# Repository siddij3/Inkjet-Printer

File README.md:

# Inkjet-Printer

DIY Inkjet Printer using Rep-Rap 3D Printing inspired parts and components

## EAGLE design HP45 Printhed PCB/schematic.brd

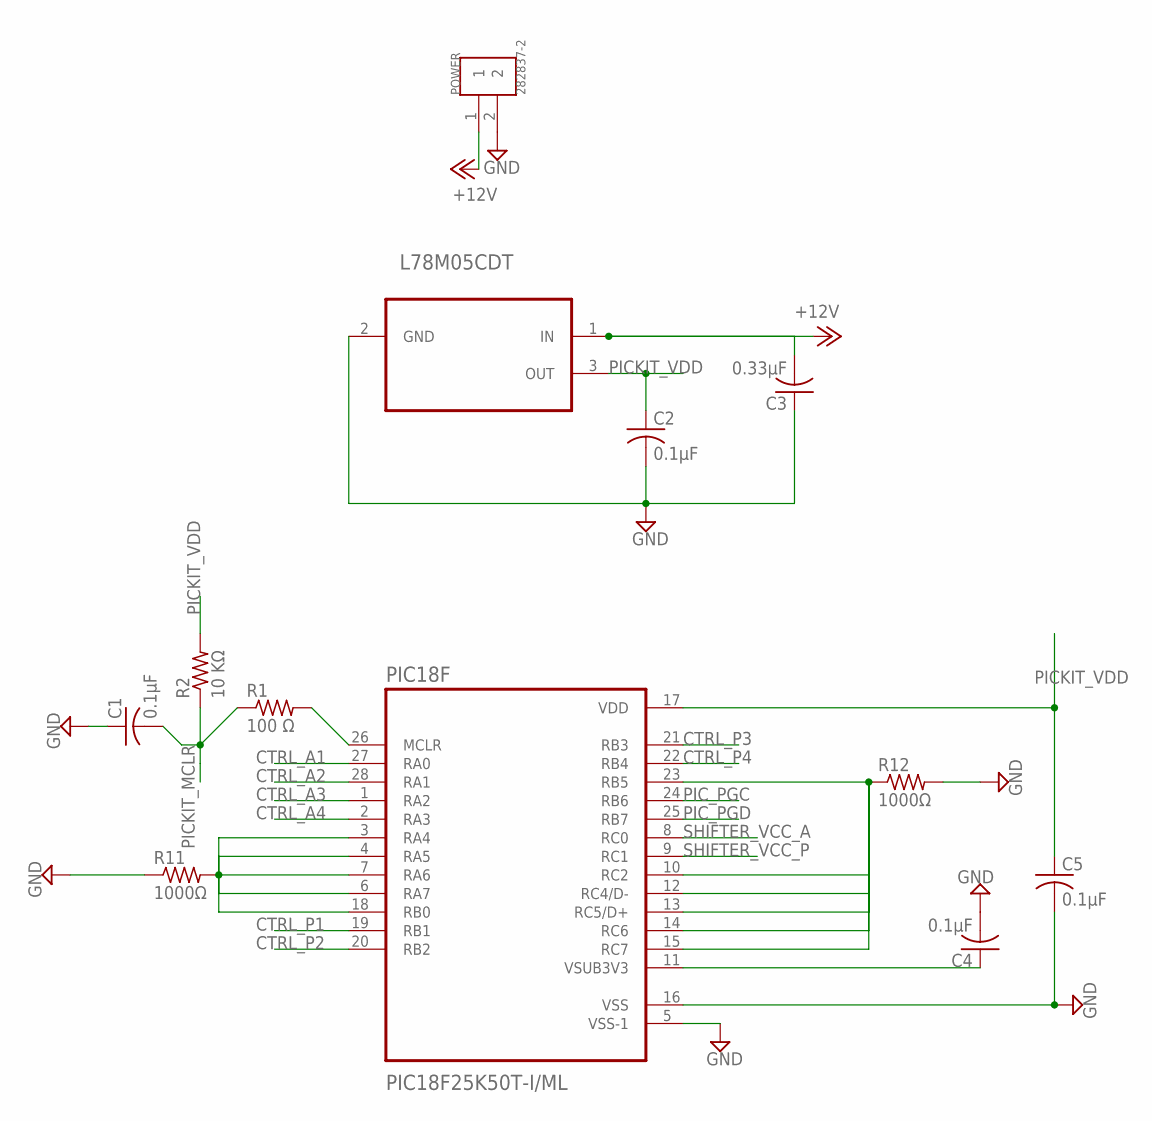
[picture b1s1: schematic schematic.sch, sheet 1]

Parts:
C1, C2, C4, C5: 0.1µF; C0603; MPN B32529C0104J000
C3: 0.33µF; C0603
L78M05CDT: L78M05CDT; TO225P972X240-3N
PIC18F: PIC18F25K50T-I/ML; QFN65P600X600X100-29N
POWER: 282837-2; TE_282837-2
R1: 100 Ω; R0805
R2: 10 KΩ; R0805
R11, R12: 1000Ω; R0603

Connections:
+12V: C3.2, L78M05CDT.1 (IN), POWER.1; also elsewhere on the board
CTRL_A1: PIC18F.27 (RA0); also elsewhere on the board
CTRL_A2: PIC18F.28 (RA1); also elsewhere on the board
CTRL_A3: PIC18F.1 (RA2); also elsewhere on the board
CTRL_A4: PIC18F.2 (RA3); also elsewhere on the board
CTRL_P1: PIC18F.19 (RB1); also elsewhere on the board
CTRL_P2: PIC18F.20 (RB2); also elsewhere on the board
CTRL_P3: PIC18F.21 (RB3); also elsewhere on the board
CTRL_P4: PIC18F.22 (RB4); also elsewhere on the board
GND: C1.1, C2.2, C3.1, C4.2, C5.2, L78M05CDT.2 (GND), PIC18F.5 (VSS-1), PIC18F.16 (VSS), POWER.2, R11.1, R12.2; also elsewhere on the board
unnamed: C4.1, PIC18F.11 (VSUB3V3)
unnamed: PIC18F.3 (RA4), PIC18F.4 (RA5), PIC18F.6 (RA7), PIC18F.7 (RA6), PIC18F.18 (RB0), R11.2
unnamed: PIC18F.26 (MCLR), R1.2
unnamed: PIC18F.10 (RC2), PIC18F.12 (RC4/D-), PIC18F.13 (RC5/D+), PIC18F.14 (RC6), PIC18F.15 (RC7), PIC18F.23 (RB5), R12.1
PICKIT_MCLR: C1.2, R1.1, R2.1; also elsewhere on the board
PICKIT_VDD: C2.1, C5.1, L78M05CDT.3 (OUT), PIC18F.17 (VDD), R2.2; also elsewhere on the board
PIC_PGC: PIC18F.24 (RB6); also elsewhere on the board
PIC_PGD: PIC18F.25 (RB7); also elsewhere on the board
SHIFTER_VCC_A: PIC18F.8 (RC0); also elsewhere on the board
SHIFTER_VCC_P: PIC18F.9 (RC1); also elsewhere on the board

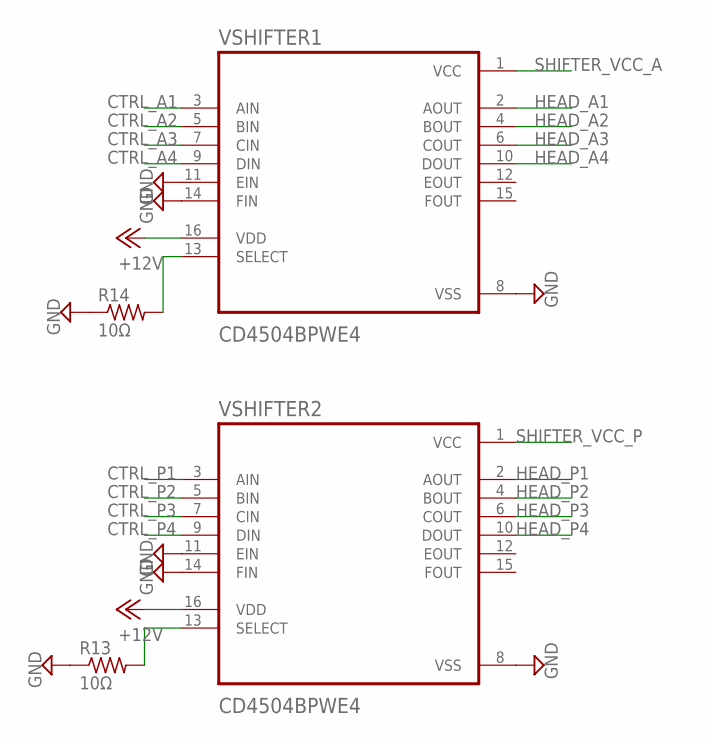
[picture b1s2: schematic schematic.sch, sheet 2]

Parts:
R13, R14: 10Ω; R0603
VSHIFTER1, VSHIFTER2: CD4504BPWE4; SOP65P640X120-16N

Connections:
+12V: VSHIFTER1.16 (VDD), VSHIFTER2.16 (VDD); also elsewhere on the board
CTRL_A1: VSHIFTER1.3 (AIN); also elsewhere on the board
CTRL_A2: VSHIFTER1.5 (BIN); also elsewhere on the board
CTRL_A3: VSHIFTER1.7 (CIN); also elsewhere on the board
CTRL_A4: VSHIFTER1.9 (DIN); also elsewhere on the board
CTRL_P1: VSHIFTER2.3 (AIN); also elsewhere on the board
CTRL_P2: VSHIFTER2.5 (BIN); also elsewhere on the board
CTRL_P3: VSHIFTER2.7 (CIN); also elsewhere on the board
CTRL_P4: VSHIFTER2.9 (DIN); also elsewhere on the board
GND: R13.1, R14.1, VSHIFTER1.8 (VSS), VSHIFTER1.11 (EIN), VSHIFTER1.14 (FIN), VSHIFTER2.8 (VSS), VSHIFTER2.11 (EIN), VSHIFTER2.14 (FIN); also elsewhere on the board
HEAD_A1: VSHIFTER1.2 (AOUT); also elsewhere on the board
HEAD_A2: VSHIFTER1.4 (BOUT); also elsewhere on the board
HEAD_A3: VSHIFTER1.6 (COUT); also elsewhere on the board
HEAD_A4: VSHIFTER1.10 (DOUT); also elsewhere on the board
HEAD_P1: VSHIFTER2.2 (AOUT); also elsewhere on the board
HEAD_P2: VSHIFTER2.4 (BOUT); also elsewhere on the board
HEAD_P3: VSHIFTER2.6 (COUT); also elsewhere on the board
HEAD_P4: VSHIFTER2.10 (DOUT); also elsewhere on the board
unnamed: R14.2, VSHIFTER1.13 (SELECT)
unnamed: R13.2, VSHIFTER2.13 (SELECT)
SHIFTER_VCC_A: VSHIFTER1.1 (VCC); also elsewhere on the board
SHIFTER_VCC_P: VSHIFTER2.1 (VCC); also elsewhere on the board

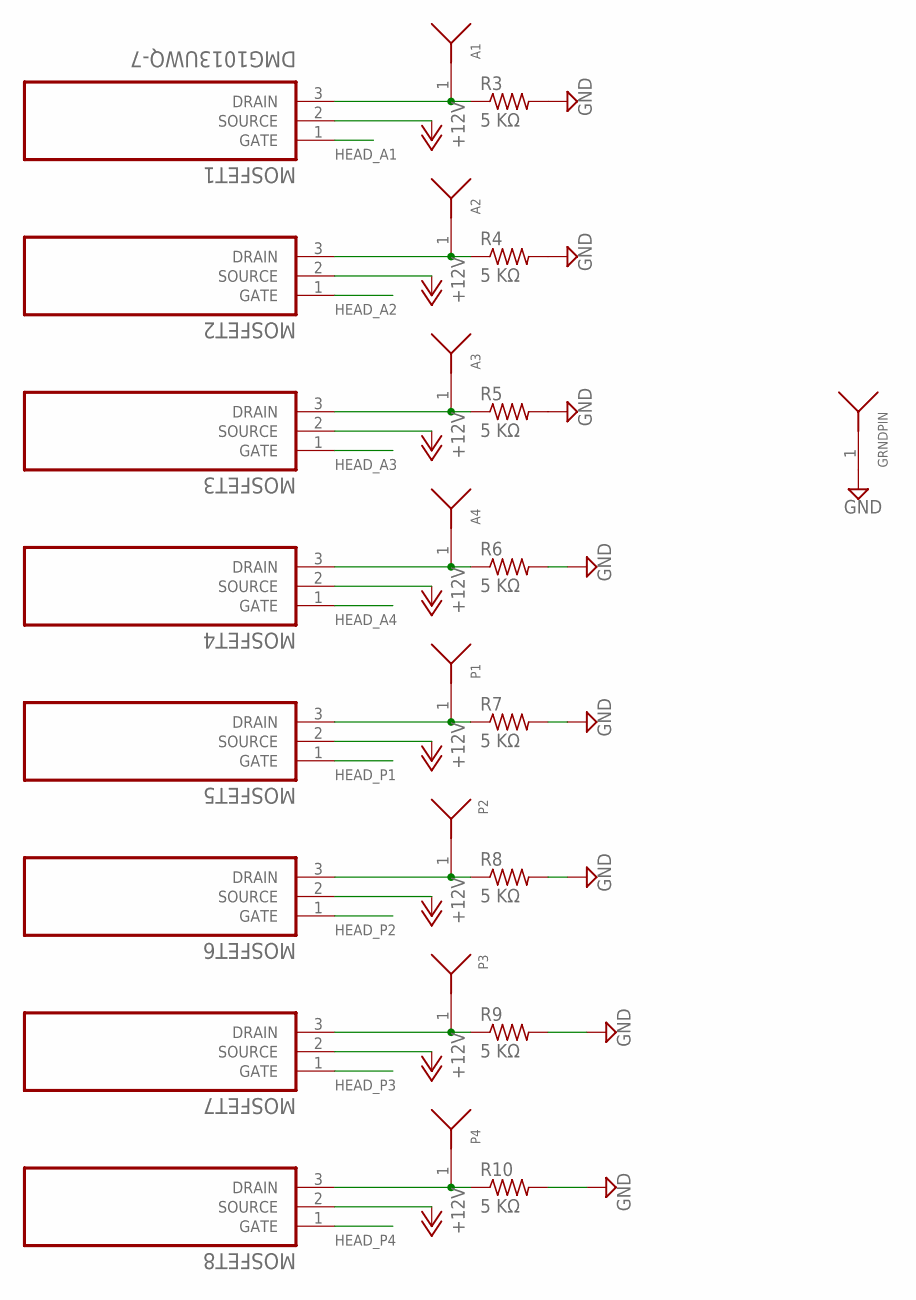
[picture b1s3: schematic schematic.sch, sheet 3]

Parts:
A1, A2, A3, A4: 0930
GRNDPIN: 0930
MOSFET1, MOSFET2, MOSFET3, MOSFET4, MOSFET5, MOSFET6, MOSFET7, MOSFET8: DMG1013UWQ-7; SOT65P210X110-3N
P1, P2, P3, P4: 0930
R3, R4, R5, R6, R7, R8, R9, R10: 5 KΩ; R0603

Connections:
+12V: MOSFET1.2 (SOURCE), MOSFET2.2 (SOURCE), MOSFET3.2 (SOURCE), MOSFET4.2 (SOURCE), MOSFET5.2 (SOURCE), MOSFET6.2 (SOURCE), MOSFET7.2 (SOURCE), MOSFET8.2 (SOURCE); also elsewhere on the board
GND: GRNDPIN.1, R3.2, R4.2, R5.2, R6.2, R7.2, R8.2, R9.2, R10.2; also elsewhere on the board
HEAD_A1: MOSFET1.1 (GATE); also elsewhere on the board
HEAD_A2: MOSFET2.1 (GATE); also elsewhere on the board
HEAD_A3: MOSFET3.1 (GATE); also elsewhere on the board
HEAD_A4: MOSFET4.1 (GATE); also elsewhere on the board
HEAD_P1: MOSFET5.1 (GATE); also elsewhere on the board
HEAD_P2: MOSFET6.1 (GATE); also elsewhere on the board
HEAD_P3: MOSFET7.1 (GATE); also elsewhere on the board
HEAD_P4: MOSFET8.1 (GATE); also elsewhere on the board
unnamed: A1.1, MOSFET1.3 (DRAIN), R3.1
unnamed: A2.1, MOSFET2.3 (DRAIN), R4.1
unnamed: A3.1, MOSFET3.3 (DRAIN), R5.1
unnamed: A4.1, MOSFET4.3 (DRAIN), R6.1
unnamed: MOSFET5.3 (DRAIN), P1.1, R7.1
unnamed: MOSFET6.3 (DRAIN), P2.1, R8.1
unnamed: MOSFET7.3 (DRAIN), P3.1, R9.1
unnamed: MOSFET8.3 (DRAIN), P4.1, R10.1

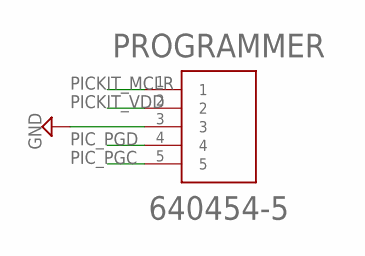
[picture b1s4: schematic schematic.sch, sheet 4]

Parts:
PROGRAMMER: 640454-5; TE_640454-5

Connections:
GND: PROGRAMMER.3; also elsewhere on the board
PICKIT_MCLR: PROGRAMMER.1; also elsewhere on the board
PICKIT_VDD: PROGRAMMER.2; also elsewhere on the board
PIC_PGC: PROGRAMMER.5; also elsewhere on the board
PIC_PGD: PROGRAMMER.4; also elsewhere on the board

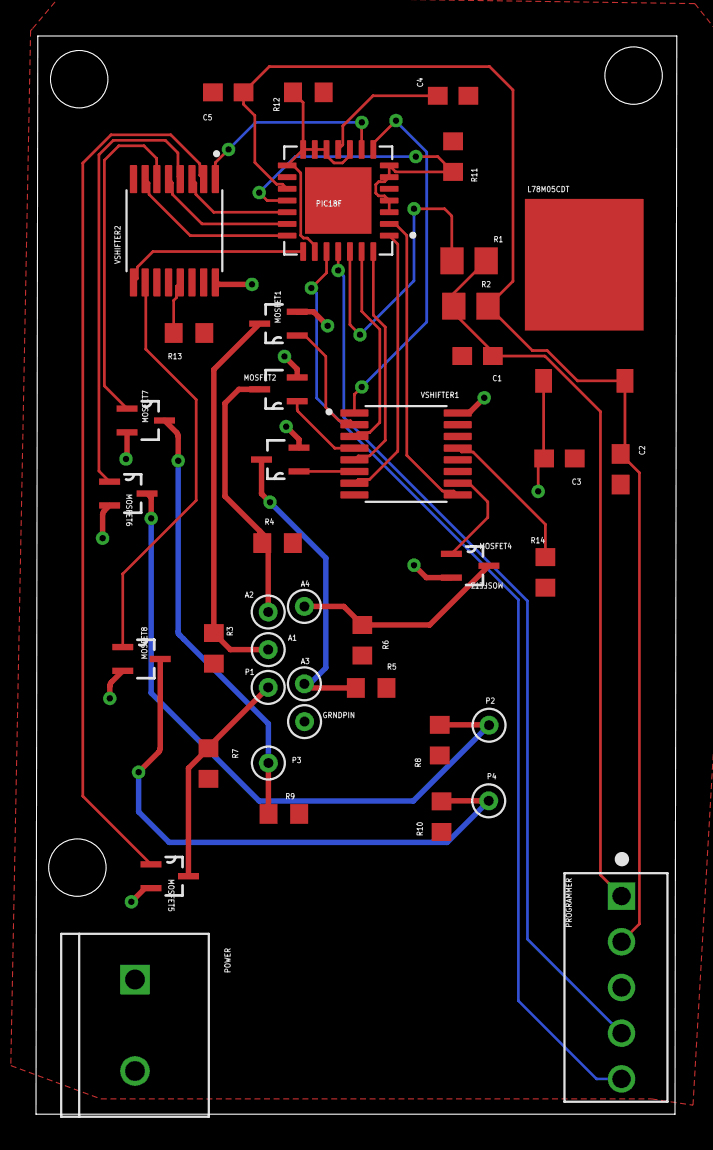
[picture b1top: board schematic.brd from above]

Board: 2 copper layers, 35.6 x 59.9 mm, 42 parts (0 on the bottom side), 38 nets.

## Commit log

2018-04-14 Prototyping
    CAD models, schematics and PIC Code
2018-04-17 PCB
    Completed board 1.0
2018-04-18 GRB File
    GRB File made and some changes to PCB (Spring loaded pins, names)
2018-04-19 PIC Code
    Using Tyler's Code
2018-04-19 PIC
    Source Files automated changes
2018-04-19 Motor Carrier
    Made the Y motor carrier
2018-04-21 temp README
2018-04-22 PCB Changes
    Revised pinheads, modified libraries
2018-04-22 PCB
    Done
2018-04-22 Done NOw?
2018-04-22 backup files
2018-04-22 Cleanup EAGLE
    Removed automatically generated backup file
2018-04-23 Minor FIx
    PCB - added Select pin from Shifter to Low Logic with 10Ω Resistor intermeditate
2018-04-23 Smaller Fixes
    Follow up for adding resistors
2018-04-23 PIC Codde
    Code that works for an N-channel MOSFET
    1 = on
    0 = off
2018-04-23 PMOS
    Code Complete for Breadboard
2018-04-26 Update
    April 26, 2018
2018-05-01 Code
    All the primitives that are on an address that need to be triggered open next. Fixed
